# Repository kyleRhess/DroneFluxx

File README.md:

# DroneFluxx

## A custom quadcopter flight controller

### Firmware

The current firmware version is tailored for an STM32F4 microcontroller. This means that it is best-suited for the related hardware, and much of this firmware is very proprietary.
\
However, the lightweight [`PID module`](https://github.com/kyleRhess/DroneFluxx/blob/master/src/PID.c) built for this project could be useful in other applications.

### Hardware

Flight controller hardware is still in work, [`but has been made public`](https://github.com/kyleRhess/DroneFluxx/tree/master/Hardware) for those who are interested.

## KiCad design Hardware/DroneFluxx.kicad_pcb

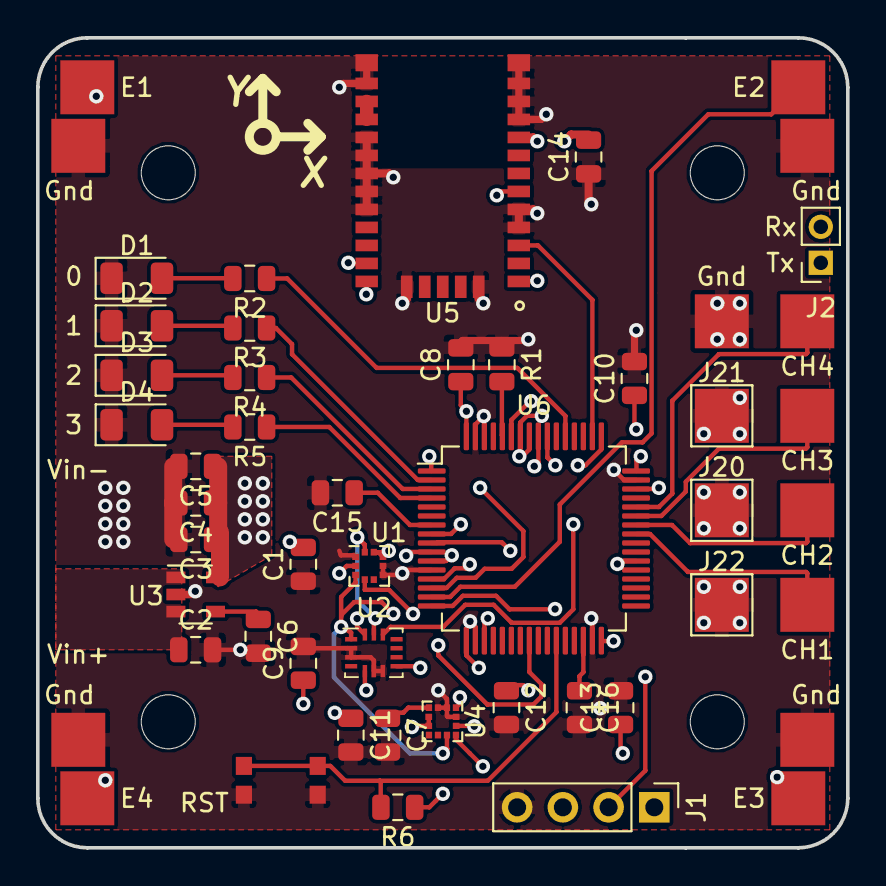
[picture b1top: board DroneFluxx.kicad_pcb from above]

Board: 4 copper layers, 45.0 x 45.0 mm, 51 parts (0 on the bottom side), 40 nets.

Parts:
C1, C4, C7, C8, C10, C11, C12, C13, C15: 0.1uF; C_0805_2012Metric
C2, C9: 1uF; C_0805_2012Metric
C3, C16: 2.2uF; C_0805_2012Metric
C5, C6: 10nF; C_0805_2012Metric
C14: 4.7uF; C_0805_2012Metric
CH1, CH2, CH3, CH4: Conn_01x01_Female; Measurement_Point_Square-SMD-Pad_Big
D1, D2, D3, D4: LED; LED_1206_3216Metric
E1, E2, E3, E4: Conn_01x01_Female; Measurement_Point_Square-SMD-Pad_Big
Gnd: Conn_01x01_Female; Measurement_Point_Square-SMD-Pad_Big
Gnd#2, Gnd#3, Gnd#4, Gnd#5: Conn_01x01_Female; Measurement_Point_Square-SMD-Pad_Big
J1: Conn_01x04_Male; PinHeader_1x04_P2.54mm_Vertical
J2: Conn_01x02_Female; PinSocket_1x02_P2.00mm_Vertical
J20, J21, J22: Conn_01x01_Female; TestPoint_Pad_3.0x3.0mm
R1, R6: 10k; R_0805_2012Metric
R2, R3, R4, R5: 470; R_0805_2012Metric
RST: SW_Push; SW_SPST_KMR2
U1: BMP388; LGA-10_2x2mm_Pitch0.5mm
U2: LSM6DSM; Bosch_LGA-14_3x2.5mm_P0.5mm
U3: LP2985-3.3; SOT-23-5
U4: LIS3MDL; LGA-12_2x2mm_P0.5mm
U5: CAM-M8C-0; 31-SMD_Module
U6: STM32F410RBTx; LQFP-64_10x10mm_P0.5mm

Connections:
+3V3: C1.2, C3.1, C4.1, C5.1, C8.1, C9.1, C10.1, C11.1, C12.1, C13.1, C14.2, J1.3, R6.1, U1.1, U1.10, U2.5, U2.8, U3.5, U4.5, U4.6, U5.1, U5.9, U6.1, U6.13, U6.19, U6.32, U6.48, U6.64
+12V: C2.1, U3.1, U3.3
ESC1: E1.1, U6.14
ESC2: E2.1, U6.15
ESC3: E3.1, U6.16
ESC4: E4.1, U6.17
GND: C1.1, C2.2, C3.2, C4.2, C5.2, C6.2, C7.2, C8.2, C9.2, C10.2, C11.2, C12.2, C13.2, C14.1, C15.2, C16.2, D1.1, D2.1, D3.1, D4.1, Gnd.1, Gnd#2.1, Gnd#3.1, Gnd#4.1, Gnd#5.1, J1.4, J20.1, J21.1, J22.1, R1.1, RST.2, U1.3, U1.8, U1.9, U2.2, U2.3, U2.6, U2.7, U3.2, U4.2, U4.3, U4.12, U5.4, U5.5, U5.10, U5.11, U5.12, U5.13, U5.14, U5.15, U5.18, U5.19, U5.20, U5.21, U5.22, U5.27, U5.31, U6.12, U6.18, U6.31, U6.47, U6.63
LED_A: R2.1, U6.53
LED_B: R3.1, U6.2
LED_C: R4.1, U6.3
LED_D: R5.1, U6.4
unnamed: C6.1, U3.4
unnamed: C7.1, U4.4
unnamed: C15.1, U6.7
unnamed: C16.1, U6.30
unnamed: D1.2, R2.2
unnamed: D2.2, R3.2
unnamed: D3.2, R4.2
unnamed: D4.2, R5.2
unnamed: R1.2, U6.60
unnamed: U5.16, U5.17
RST_SW: R6.2, RST.1, U6.27
Rx_CH1: CH1.1, U6.41
Rx_CH2: CH2.1, U6.42
Rx_CH3: CH3.1, U6.43
Rx_CH4: CH4.1, U6.44
SPI1_CLK: U5.6, U6.55
SPI1_CS0: U5.3, U6.50
SPI1_MISO: U5.25, U6.56
SPI1_MOSI: U5.26, U6.57
SPI2_CLK: U1.2, U2.13, U4.1, U6.38
SPI2_CS0: U2.12, U6.8
SPI2_CS1: U4.10, U6.9
SPI2_CS2: U1.6, U6.24
SPI2_MISO: U1.5, U2.1, U4.9, U6.10
SPI2_MOSI: U1.4, U2.14, U4.11, U6.11
SWCLK: J1.2, U6.49
SWDIO: J1.1, U6.46
USART1_RX: J2.2, U6.59
USART1_TX: J2.1, U6.58

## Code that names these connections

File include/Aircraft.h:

#ifndef AIRCRAFT_H_ /* include guard */
#define AIRCRAFT_H_

#include <stdio.h>

typedef int bool;
#define true 1
#define false 0

#define MOTOR_ESC_1 	TIM_CHANNEL_1 //e3
#define MOTOR_ESC_2 	TIM_CHANNEL_2
#define MOTOR_ESC_3 	TIM_CHANNEL_3 //e4
#define MOTOR_ESC_4 	TIM_CHANNEL_4

#define CHANNEL_1_ROLL 	0
#define CHANNEL_2_PITCH 1
#define CHANNEL_3_YAW 	2
#define CHANNEL_4_THOT 	3
#define CHANNEL_NUM 	4

#define SAMPLE_RATE_HZ(xxx) (SAMPLE_RATE / xxx)

typedef enum
{
	LED_A = 0,
	LED_B = 1,
	LED_C = 2,
	LED_D = 3
} CRAFT_LED;

typedef enum
{
	AIRCRAFT_STATE_NONE = -1,
	AIRCRAFT_STATE_INIT,
	AIRCRAFT_STATE_TX_CAL,
	AIRCRAFT_STATE_IDLE,
	AIRCRAFT_STATE_ALIGNING,
	AIRCRAFT_STATE_ARMED,
	AIRCRAFT_STATE_DISARMED
} CRAFT_STATE;

extern volatile CRAFT_STATE AIRCRAFT_STATE;

extern float alt_Ahrs;
extern float roll_Ahrs;
extern float pitch_Ahrs;
extern float yaw_Ahrs;
extern float xgyro_Ahrs;
extern float ygyro_Ahrs;
extern float zgyro_Ahrs;
extern float xaccl_Ahrs;
extern float yaccl_Ahrs;
extern float zaccl_Ahrs;
extern float roll_Input;
extern float pitch_Input;
extern float yaw_Input;
extern float throt_Input;
extern float alpha_Yaw;
extern float throttleBias;
extern float yawBias;
extern float pitchBias;
extern float rollBias;

extern uint8_t flashFreq[4];

void aircraft_GetRxInput(void);
bool aircraft_CalibratingInput(void);
bool aircraft_IsCalibrated(void);
bool aircraft_IsFlying(void);
bool aircraft_Disarming(void);
bool aircraft_Arming(void);
void aircraft_UpdateMotors(void);
void aircraft_Set_LED(int);
void aircraft_Reset_LED(int);
void aircraft_WriteLED(int, int);
void aircraft_FlashLED(int, uint8_t);
void aircraft_Reset(void);

#endif

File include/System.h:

#ifndef SYSTEM_H_ /* include guard */
#define SYSTEM_H_

#include <stdio.h>
#include "stm32f4xx.h"
#include "SPI.h"
#include "PID.h"
#include "PWM.h"
#include "MadgwickAHRS.h"
#include "Data.h"
#include "Aircraft.h"
#include "Receiver.h"
#include "Reset.h"
#include "Serial.h"
#include "IMU.h"
#include "Baro.h"

#define IMU_ENABLED
//#define IMU_MAGS
#define GPS_ENABLED
#define BARO_ENABLED

//#define PID_RATE

#define ATT_SCALE 1.0f
#define RATE_SCALE 3.0f

#define HIGH 			1
#define LOW  			0
typedef int bool;

#define SYS_READ_TIME(xxx) 	((float)(xxx) / (float)SAMPLE_RATE)
#define SQR(xxx) 			((xxx) * (xxx))

#define SAMPLE_RATE 	5000 //Hz
#define CONTROL_RATE 	1000 //Hz
#define PI 				3.1415926535897f
#define ACCL_SCALE		16.0f  	//g's
#define GYRO_SCALE 		2000.0f //dps
#define MAG_SCALE 		8.0f 	//gauss

#define MIN_THROT		6.0f
#define MIN_ESC_US		5.0f
#define MAX_ESC_US		25.0f

// SPI port mapping
#define SPI1_CS_PORT	GPIOA
#define SPI1_CS0		GPIO_PIN_15
#define SPI2_CS_PORT	GPIOC
#define SPI2_CS0		GPIO_PIN_0
#define SPI2_CS1		GPIO_PIN_1
#define SPI2_CS2		GPIO_PIN_4

// MAG Defs
#define MAG_WHO_AM_I	0x0f
#define MAG_CTRL_REG1	0x20
#define MAG_CTRL_REG1_V	0x7c
#define MAG_CTRL_REG2	0x21
#define MAG_CTRL_REG2_V	0x20
#define MAG_CTRL_REG3	0x22
#define MAG_CTRL_REG3_V	0x00
#define MAG_CTRL_REG4	0x23
#define MAG_CTRL_REG4_V	0x0c
#define MAG_CTRL_REG5	0x24
#define MAG_CTRL_REG5_V	0x00
#define MAG_OUT_X_L		0x28
#define MAG_OUT_X_H		0x29
#define MAG_OUT_Y_L		0x2a
#define MAG_OUT_Y_H		0x2b
#define MAG_OUT_Z_L		0x2c
#define MAG_OUT_Z_H		0x2d
#define MAG_TEMP_OUT_L	0x2e
#define MAG_TEMP_OUT_H	0x2f

// BARO Defs
#define BARO_WHO_AM_I	0x00
#define BARO_FIFO_CNFIG	0x17
#define BARO_PWR_CTRL	0x1B
#define BARO_OSR		0x1C
#define BARO_ODR		0x1D
#define BARO_CONFIG		0x1F
#define BARO_IF_CONF	0x1A
#define BARO_PDATA_0	0x04
#define BARO_PDATA_1	0x05
#define BARO_PDATA_2	0x06
#define BARO_TDATA_0	0x07
#define BARO_TDATA_1	0x08
#define BARO_TDATA_2	0x09
#define BARO_SENSTIME_0	0x0C
#define BARO_SENSTIME_1	0x0D
#define BARO_SENSTIME_2	0x0E

#define RWBIT 			0x7f
#define MSBIT 			0xbf

#define ERROR_IMU		0x01
#define ERROR_BARO		0x02
#define ERROR_GPS		0x04
#define ERROR_MAG		0x08


typedef enum
{
	MOTOR_FRONT_LEFT = 0,
	MOTOR_FRONT_RIGHT,
	MOTOR_BACK_LEFT,
	MOTOR_BACK_RIGHT,
	MOTOR_NUM
} MOTORS;

typedef enum
{
	PID_PITCH = 0,
	PID_ROLL,
	PID_YAW,
	PID_ALT,
	PID_NUM
} PID_CONTROLLERS_ANGLE;

typedef enum
{
	PID_XGYR = PID_PITCH,
	PID_YGYR,
	PID_ZGYR
} PID_CONTROLLERS_RATE;

typedef enum
{
	SYS_STATE_NONE = -1,
	SYS_STATE_IDLE,
	SYS_STATE_PROCESSING,
	SYS_STATE_CONTROLLING,
	SYS_STATE_RESET
} SYS_STATE;

extern volatile SYS_STATE SYSTEM_STATE;

extern float channelPulseWidth_us[CHANNEL_NUM];
extern PWM_Out PWMtimer;

extern PID_Controller flightControl[PID_NUM];
extern float motorPower[MOTOR_NUM];

extern float proportionalGain[PID_NUM];
extern float integralGain[PID_NUM];
extern float derivativeGain[PID_NUM];

extern float proportionalGain[PID_NUM];
extern float integralGain[PID_NUM];
extern float derivativeGain[PID_NUM];

extern DMA_HandleTypeDef hdma_usart1_rx;

void RunSystem();
void runController();
void resetController();

int InitializeSystem(void);
int InitPWMOutput(void);
int InitPID(void);

extern float mapVal(float x, float in_min, float in_max, float out_min, float out_max);


#endif /* SYSTEM_H_ */

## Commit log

2020-01-22 Added library files
2020-01-22 Code cleanup
2020-01-23 Added readme
2020-01-25 Added hardware files.
2020-01-25 Cleaned hardware files.
2020-01-27 Updated hardware to use latest library references.
2020-02-11 Unused code cleanup.
    -Extract all Mag functions into Mag.c since not using Mag for now.
    -Extract all GPS functions into GPS.c since not using GPS for now.
    -Get rid of "angle control" in Aircraft.c
    -Moved processing of IMU and baro data into their respective .C files
    -Perform general code cleanup and commenting.
2020-02-14 Simplified disarming procedure.
    -Moved LED flashing to Data.c ISR for consistency.
    -Removed some unsed variables
    -Decreased disarming time
    -General code clean-up
2020-02-19 Fixed UART receiver
    Eliminated use of "HAL_UART_Receive_IT" and instead get UART data on a single byte interrupt. This allows receiving any number of bytes.
2020-07-16 Code cleanup.
    Removed some redundancy and fixed some formatting.
2021-07-08 Replaced arbitrary value. Fixes #1
2021-07-08 Updated PID library to use a more robust integrator windup guard. Fixes #2
2021-07-27 Fix typo
